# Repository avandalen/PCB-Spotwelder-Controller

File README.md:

This advanced controller was used by many people and has a unique reduced inrush current circuit that prevents main fuse blow up. This product is no longer for sale since 7-2020. 
See the article here: https://www.avdweb.nl/popular/spotwelder/spot-welder-controller-with-tft-display

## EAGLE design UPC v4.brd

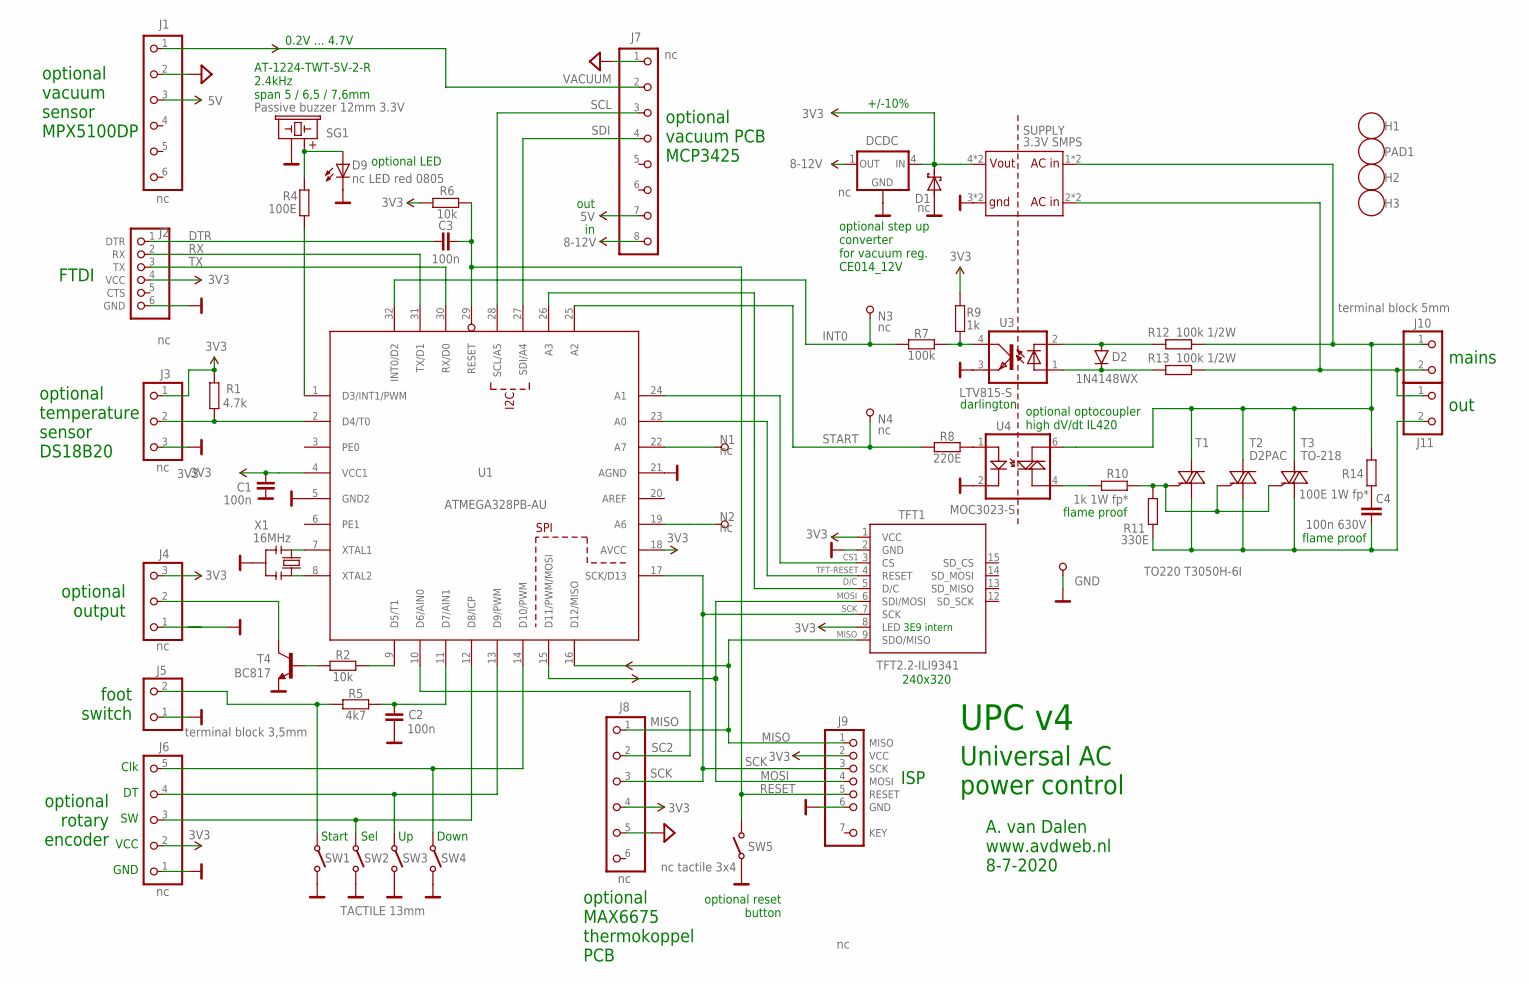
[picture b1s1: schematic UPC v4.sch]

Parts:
C1, C2, C3: 100n; 0603-SMALL
C4: 100n 630V; C15B6
D1: nc; DO-214AC
D2: 1N4148WX; SOD-323
D9: nc LED red 0805; CHIP-LED0805
DCDC: nc; 1X04-ACDC
GND: GND; PIN
H1, H2, H3: HOLE3.6; HOLE-3.6MM
J1: nc; MPX5100-VACUUM-SENSOR
J2: nc; ZIGZAG-FTDI
J3, J4: nc; 1X03
J5: terminal block 3,5mm; SCREWTERMINAL-3.5MM-2
J6: nc; 1X05
J7: nc; 1X08
J8: nc; 1X06-ISP-BOARD
J9: nc; ZIGZAG-ISP
J10: Terminal block 5mm 2p; SCREWTERMINAL-5MM-2
J11: terminal block 5mm; SCREWTERMINAL-5MM-2
N1, N2, N3, N4: nc; PIN-1.2MM
PAD1: HOLE3.6; HOLE-3.6MM
R1: 4.7k; 0603-SMALL
R2, R6: 10k; 0603-SMALL
R4: 100E; 0603-SMALL
R5: 4k7; 0603-SMALL
R7: 100k; 0603-SMALL
R8: 220E; 0603-SMALL
R9: 1k; 0603-SMALL
R10: 1k 1W fp*; 0411/15_AVD
R11: 330E; 0603-SMALL
R12, R13: 100k 1/2W; M1206
R14: 100E 1W fp*; 0411/15_AVD
SG1: Passive buzzer 12mm 3.3V; BUZZER-12MM-NS-KIT
SUPPLY: 3.3V SMPS; SMPS2
SW1, SW2, SW3, SW4: TACTILE 13mm; TACTILE-PTH
SW5: nc tactile 3x4; TACTILE-3X4
T1: TO220 T3050H-6I; TO220-SPOTWELDER
T2: D2PAC; D2PACK-SPOTWELDER-NO-CREAM
T3: TO-218; TO218-SPOTWELDER
T4: BC817; SOT23-3
TFT1: TFT2.2-ILI9341; TFT2.2-9P
U1: ATMEGA328PB-AU; TQFP32-08
U3: LTV815-S; DIL4-SMD
U4: MOC3023-S; DIL6-SMD-WIDE
X1: 16MHz; RESONATOR

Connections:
3V3: C1.2, D1.C, DCDC.4 (IN), J2.4 (VCC), J3.1, J4.3, J6.2, J8.4, J9.2 (VCC), R1.1, R6.2, R9.2, SUPPLY.4 (5V), SUPPLY.7 (5V), TFT1.1 (VCC), TFT1.8 (LED), U1.4 (VCC1), U1.18 (AVCC)
5V: J1.3, J7.7
8-12V: DCDC.1 (OUT), J7.8
AGND: J1.2, J7.1, J8.5
BUZZER: R4.2, U1.1 (D3/INT1/PWM)
BUZZER+: D9.A, R4.1, SG1.+1 (+), SG1.+2 (+)
CS1: TFT1.3 (CS), U1.24 (A1)
D/C: TFT1.5 (D/C), U1.26 (A3)
DOWN: J6.3, SW2.3, SW2.4, U1.12 (D8/ICP)
DTR: C3.1, J2.1 (DTR)
FOOT1: J5.2, R5.1, SW1.3, SW1.4
FOOT2: C2.2, R5.2, U1.11 (D7/AIN1)
GND: C1.1, C2.1, D1.A, D9.C, DCDC.2 (GND), DCDC.3 (GND), GND.1, J2.6 (GND), J3.3, J4.1, J5.1, J6.1, J9.6 (GND), SG1.-1 (-), SG1.-2 (-), SUPPLY.3 (GND), SUPPLY.5 (GND), SW1.1 (O), SW1.2 (O), SW2.1 (O), SW2.2 (O), SW3.1 (O), SW3.2 (O), SW4.1 (O), SW4.2 (O), SW5.2, T4.2 (E), TFT1.2 (GND), U1.5 (GND2), U1.21 (AGND), U3.3 (EMIT), U4.2, X1.2
INT0: N3.1, R7.1, U1.32 (INT0/D2)
MAINS1: J10.2, J11.1, R13.2, SUPPLY.2 (AC2), SUPPLY.8 (AC2)
MAINS2: J10.1, R12.2, R14.2, SUPPLY.1 (AC1), SUPPLY.9 (AC1), T1.2 (A2), T2.TAB (A2), T3.2 (A2), U4.6
MISO: J8.1, J9.1 (MISO), TFT1.9 (SDO/MISO), U1.16 (D12/MISO)
MOSI: J9.4 (MOSI), TFT1.6 (SDI/MOSI), U1.15 (D11/PWM/MOSI)
unnamed: R10.1, U4.4
unnamed: R2.1, T4.1 (B)
unnamed: N2.1, U1.19 (A6)
unnamed: N1.1, U1.22 (A7)
unnamed: R8.2, U4.1
unnamed: D2.A, R12.1, U3.2 (C)
unnamed: D2.C, R13.1, U3.1 (A)
unnamed: U1.7 (XTAL1), X1.1
unnamed: C4.1, R14.1
unnamed: J4.2, T4.3 (C)
unnamed: R2.2, U1.9 (D5/T1)
unnamed: R7.2, R9.1, U3.4 (COL)
unnamed: U1.8 (XTAL2), X1.3
Q1-C: C4.2, C4.3 (2), J11.2, R11.1, T1.1 (A1), T2.1 (A1), T3.1 (A1)
Q1-G: R10.2, R11.2, T1.3 (G), T2.3 (G), T3.3 (G)
RESET: C3.2, J9.5 (RESET), R6.1, SW5.1 (O), U1.29 (RESET)
RX: J2.2 (RX), U1.31 (TX/D1)
SC2: J8.2, U1.10 (D6/AIN0)
SCK: J8.3, J9.3 (SCK), TFT1.7 (SCK), U1.17 (SCK/D13)
SCL: J7.3, U1.28 (SCL/A5)
SDI: J7.4, U1.27 (SDI/A4)
SEL: J6.5, SW4.3, SW4.4, U1.14 (D10/PWM)
START: N4.1, R8.1, U1.25 (A2)
TEMP: J3.2, R1.2, U1.2 (D4/T0)
TFT-RESET: TFT1.4 (RESET), U1.23 (A0)
TX: J2.3 (TX), U1.30 (RX/D0)
UP: J6.4, SW3.3, SW3.4, U1.13 (D9/PWM)
VACUUM: J1.1, J7.2

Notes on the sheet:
mains
out
foot switch
Universal AC power control
Start
Sel
Down
flame proof
240x320
A. van Dalen www.avdweb.nl 8-7-2020
3E9 intern
ISP
optional optocoupler high dV/dt IL420
optional vacuum sensor MPX5100DP
optional vacuum PCB MCP3425
optional temperature sensor DS18B20
+/-10%
optional step up converter for vacuum reg. CE014_12V
optional MAX6675 thermokoppel PCB
optional reset button
AT-1224-TWT-5V-2-R 2.4kHz span 5 / 6,5 / 7,6mm
optional rotary encoder
Clk
VCC
GND
FTDI
optional output
optional LED
UPC v4
darlington
0.2V ... 4.7V

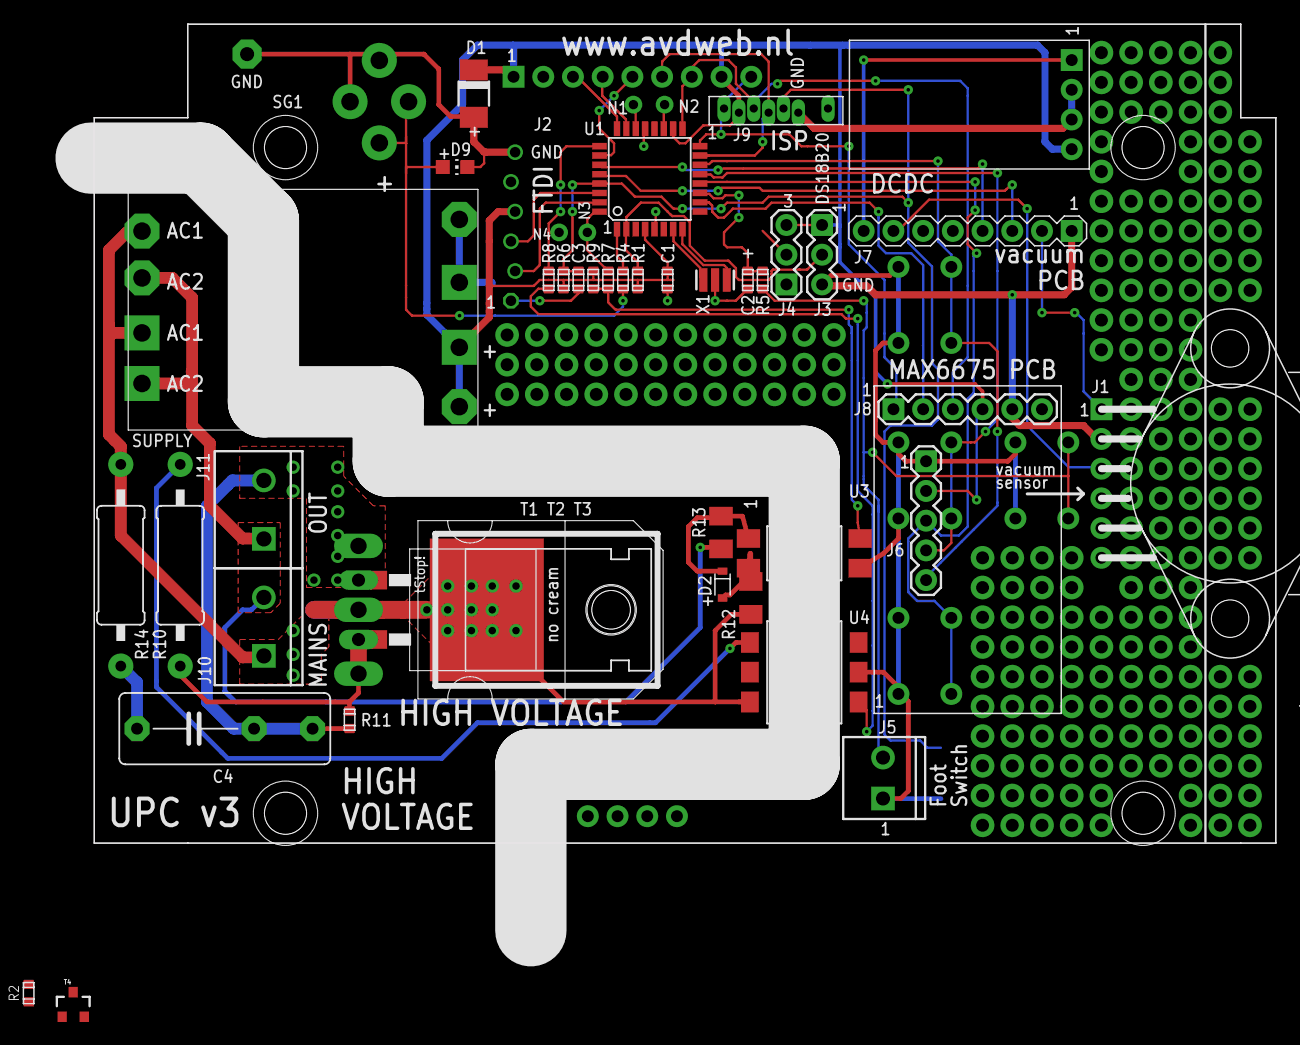
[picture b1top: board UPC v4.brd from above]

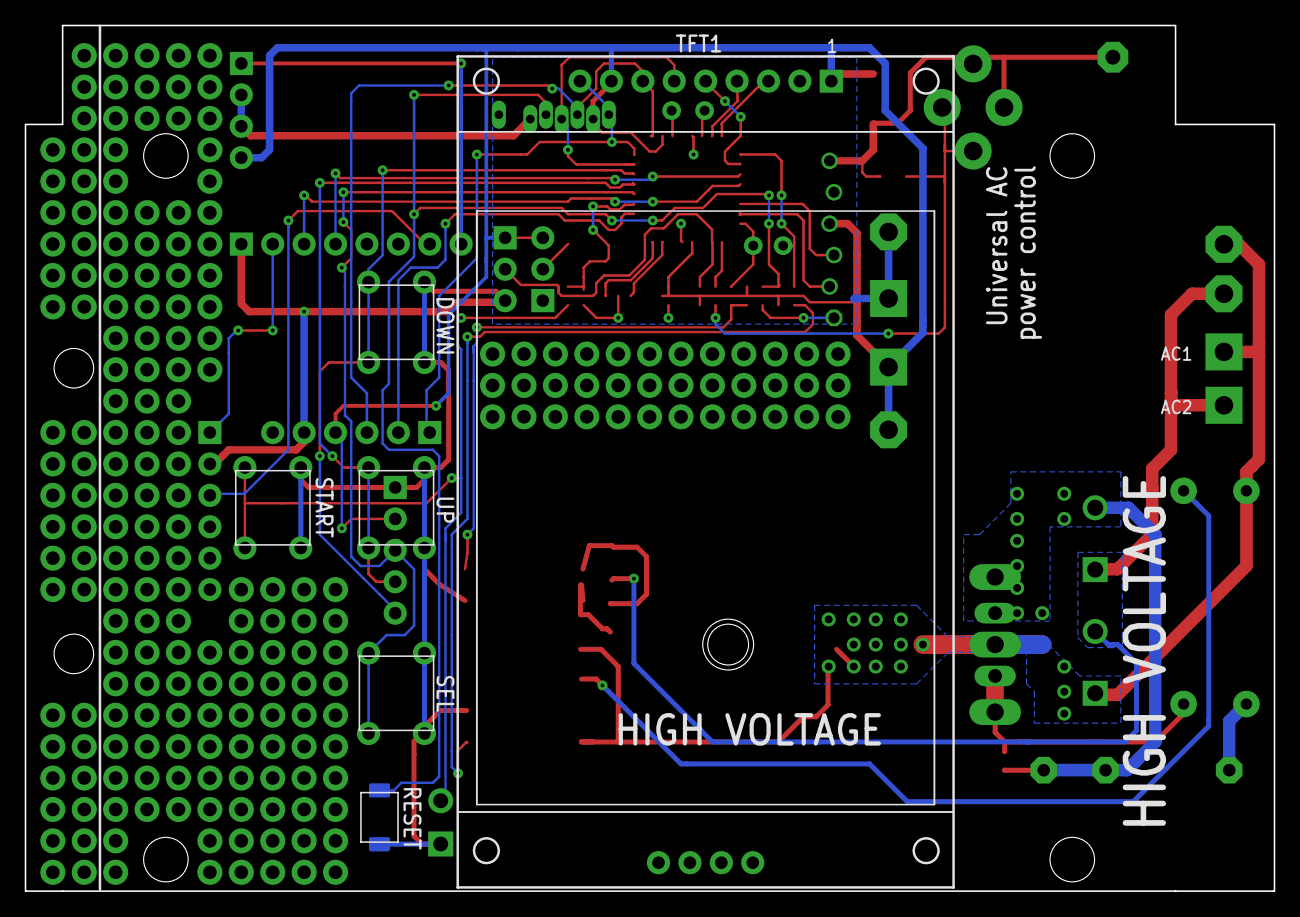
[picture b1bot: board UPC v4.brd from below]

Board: 2 copper layers, 101.0 x 70.0 mm, 57 parts (6 on the bottom side), 46 nets.

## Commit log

2021-05-24 Create LICENSE

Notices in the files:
parts and their libraries:
SparkFun-DiscreteSemi: Licensing: Creative Commons ShareAlike 4.0 International - https://creativecommons.org/licenses/by-sa/4.0
